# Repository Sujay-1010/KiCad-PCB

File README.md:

# KiCad-PCB
All the projects given have their pcb designing as well as their schematics attached.

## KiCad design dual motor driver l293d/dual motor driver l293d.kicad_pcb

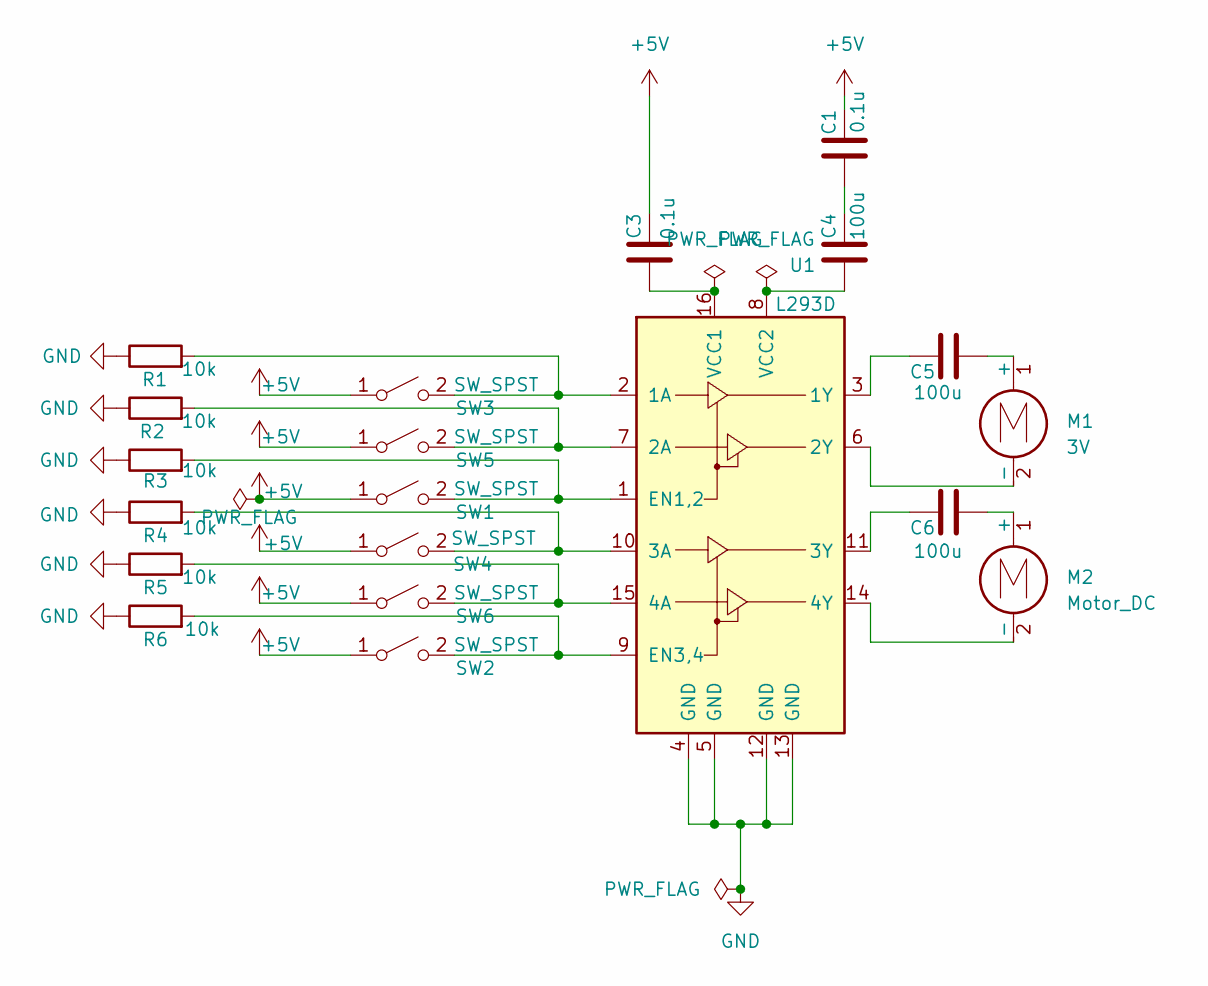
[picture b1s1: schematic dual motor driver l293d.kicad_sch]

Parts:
C1, C3: 0.1u; CP_Axial_L10.0mm_D6.0mm_P15.00mm_Horizontal
C4, C5, C6: 100u; CP_Axial_L10.0mm_D6.0mm_P15.00mm_Horizontal
M1: 3V; Vybronics_VZ30C1T8219732L
M2: Motor_DC; Vybronics_VZ30C1T8219732L
R1, R2, R3, R4, R5, R6: 10k; resistor
SW1, SW2, SW3, SW4, SW5, SW6: SW_SPST; SW_Push_1P1T_NO_CK_KMR2
U1: L293D; DIP-16_W7.62mm

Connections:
+5V: C1.2, C3.2, SW1.1 (A), SW2.1 (A), SW3.1 (A), SW4.1 (A), SW5.1 (A), SW6.1 (A)
GND: R1.1, R2.1, R3.1, R4.1, R5.1, R6.1, U1.4 (GND), U1.5 (GND), U1.12 (GND), U1.13 (GND)
unnamed: C1.1, C4.2
unnamed: C5.1, M1.1 (+)
unnamed: M1.2 (-), U1.6 (2Y)
unnamed: C6.1, M2.1 (+)
unnamed: M2.2 (-), U1.14 (4Y)
unnamed: R3.2, SW1.2 (B), U1.1 (EN1,2)
unnamed: R6.2, SW2.2 (B), U1.9 (EN3,4)
unnamed: R1.2, SW3.2 (B), U1.2 (1A)
unnamed: R4.2, SW4.2 (B), U1.10 (3A)
unnamed: R2.2, SW5.2 (B), U1.7 (2A)
unnamed: R5.2, SW6.2 (B), U1.15 (4A)
unnamed: C5.2, U1.3 (1Y)
unnamed: C6.2, U1.11 (3Y)
unnamed: C3.1, U1.16 (VCC1)
unnamed: C4.1, U1.8 (VCC2)

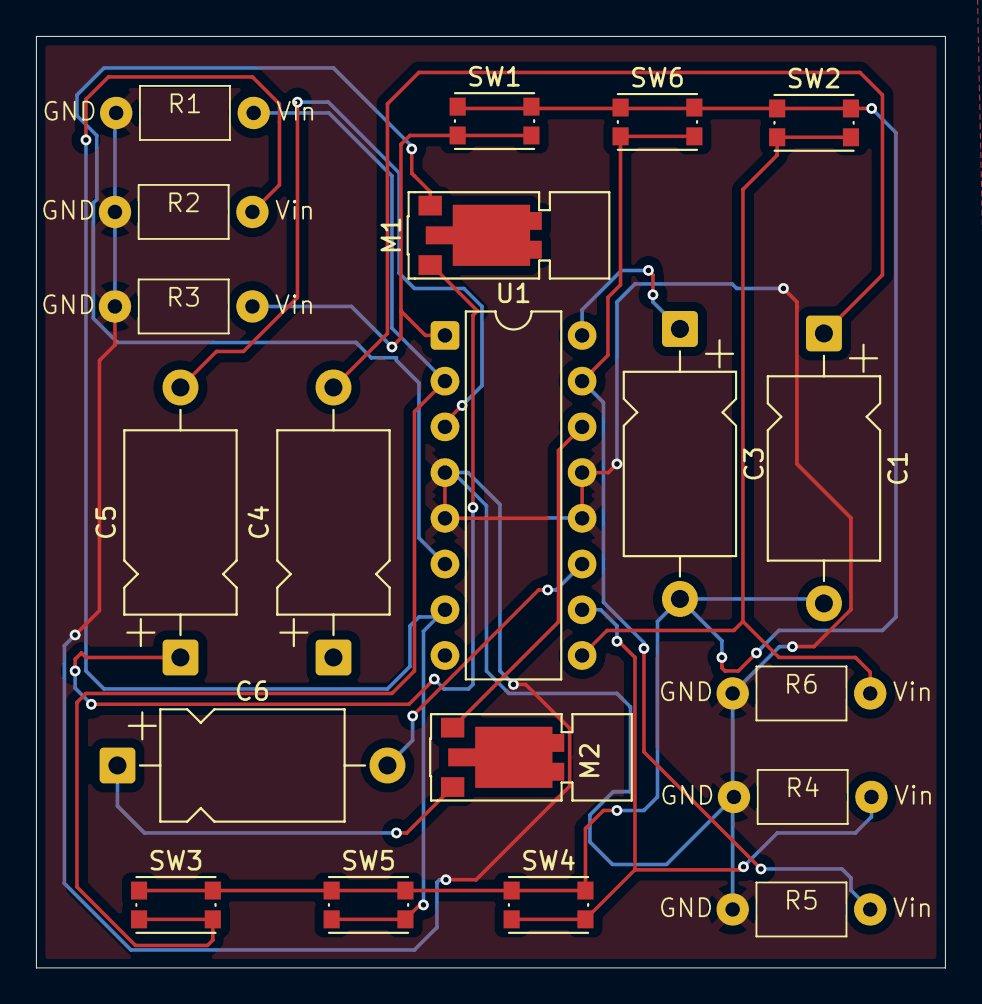
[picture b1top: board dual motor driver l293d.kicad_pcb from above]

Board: 2 copper layers, 50.5 x 51.8 mm, 20 parts (0 on the bottom side), 17 nets.

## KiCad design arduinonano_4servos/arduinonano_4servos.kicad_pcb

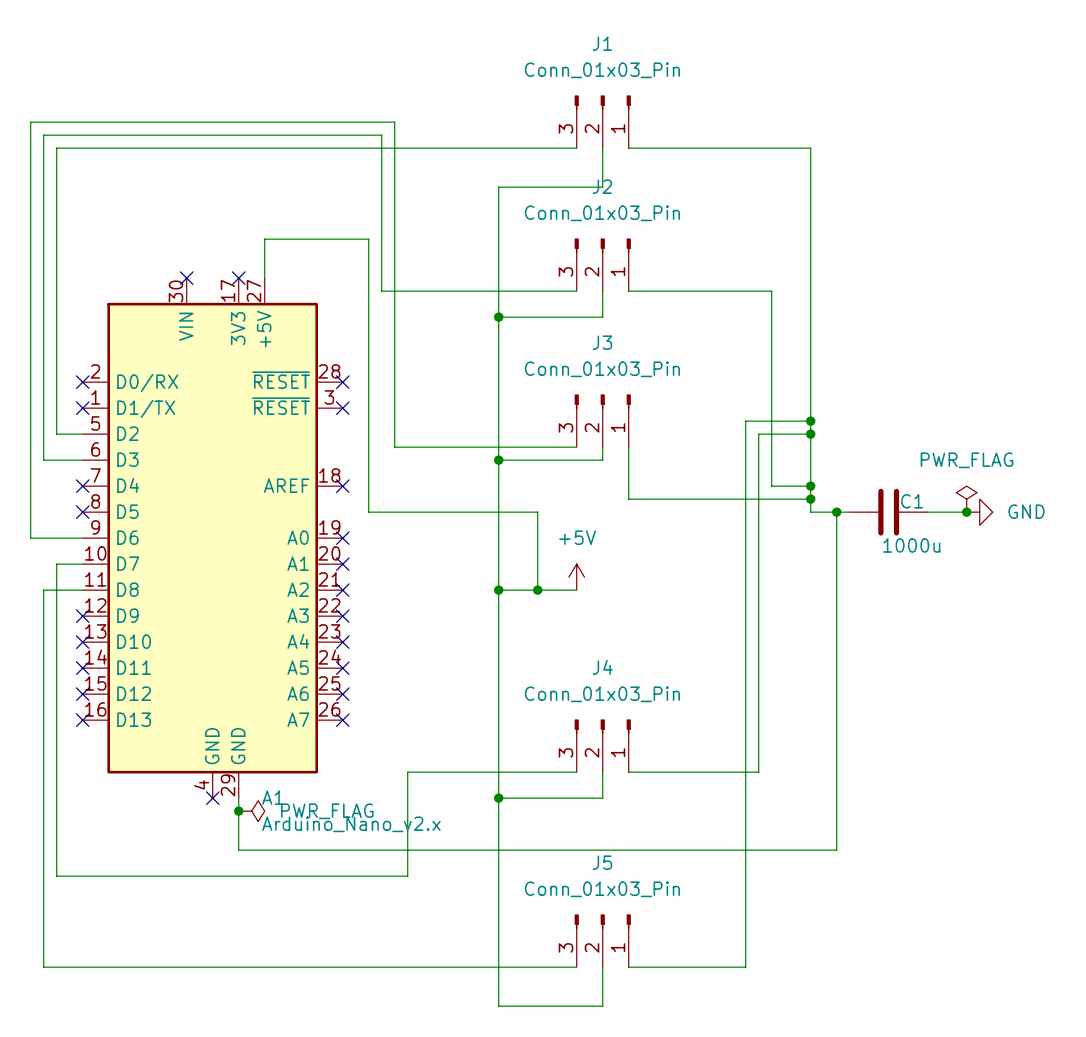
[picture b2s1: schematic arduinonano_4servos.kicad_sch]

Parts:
A1: Arduino_Nano_v2.x; Arduino_Nano
C1: 1000u; C_Disc_D6.0mm_W2.5mm_P5.00mm
J1, J2, J3, J4, J5: Conn_01x03_Pin; PinHeader_1x03_P2.54mm_Vertical

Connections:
+5V: A1.27 (+5V), J1.2, J2.2, J3.2, J4.2, J5.2
GND: C1.2
unnamed: A1.5 (D2), J1.3
unnamed: A1.6 (D3), J2.3
unnamed: A1.9 (D6), J3.3
unnamed: A1.10 (D7), J4.3
unnamed: A1.11 (D8), J5.3
unnamed: A1.29 (GND), C1.1, J1.1, J2.1, J3.1, J4.1, J5.1

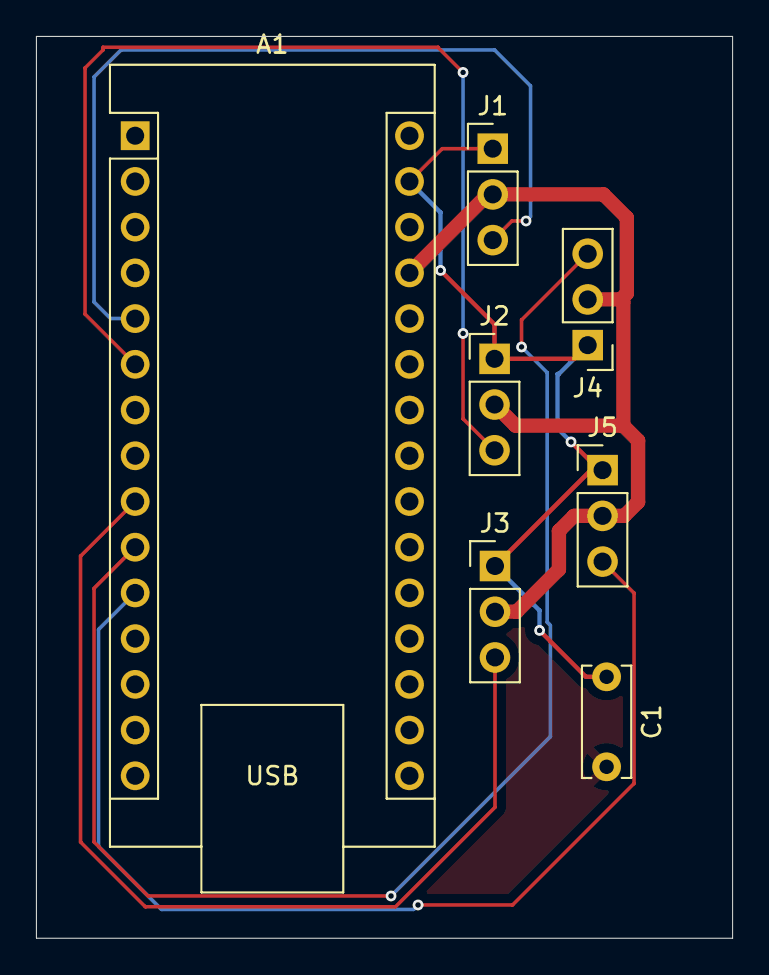
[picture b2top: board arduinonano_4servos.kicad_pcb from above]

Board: 2 copper layers, 38.7 x 50.1 mm, 7 parts (0 on the bottom side), 7 nets.

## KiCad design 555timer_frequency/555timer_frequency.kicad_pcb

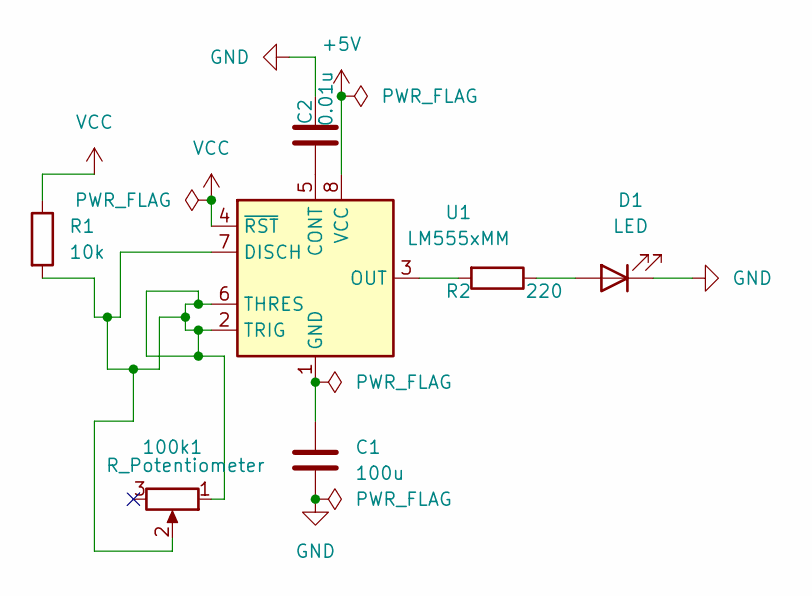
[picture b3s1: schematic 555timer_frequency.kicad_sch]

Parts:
100k1: R_Potentiometer; Potentiometer_ACP_CA9-H3,8_Horizontal
C1: 100u; C_Disc_D5.0mm_W2.5mm_P5.00mm
C2: 0.01u; C_Disc_D5.0mm_W2.5mm_P5.00mm
D1: LED; led
R1: 10k; resistor
R2: 220; resistor
U1: LM555xMM; VSSOP-8_3x3mm_P0.65mm

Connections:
+5V: U1.8 (VCC)
GND: C1.2, C2.2, D1.1 (K)
unnamed: D1.2 (A), R2.1
unnamed: C2.1, U1.5 (CONT)
unnamed: 100k1.1, 100k1.2, R1.2, U1.2 (TRIG), U1.6 (THRES), U1.7 (DISCH)
unnamed: C1.1, U1.1 (GND)
unnamed: R2.2, U1.3 (OUT)
VCC: R1.1, U1.4 (~RST)

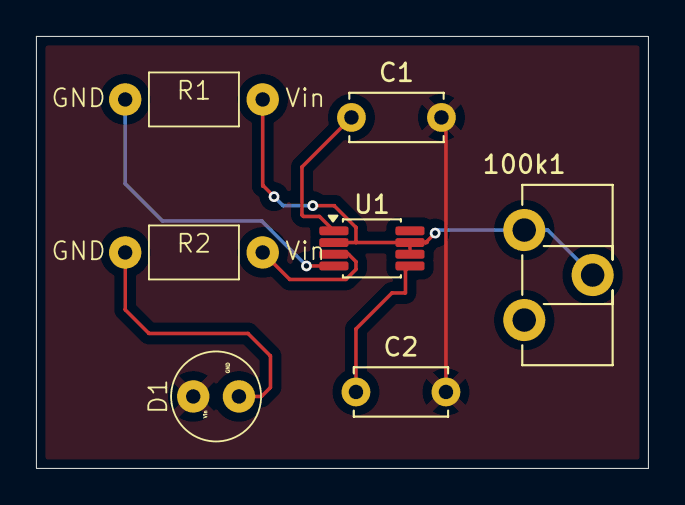
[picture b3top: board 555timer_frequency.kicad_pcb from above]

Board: 2 copper layers, 34.0 x 24.0 mm, 7 parts (0 on the bottom side), 7 nets.

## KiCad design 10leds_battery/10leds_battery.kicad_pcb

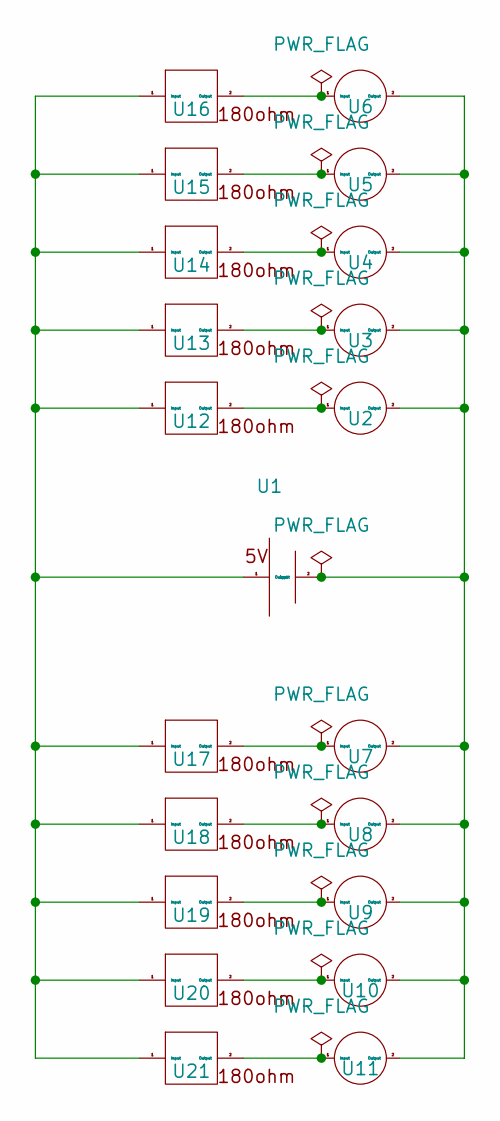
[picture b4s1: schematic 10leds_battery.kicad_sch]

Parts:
U1: battery
U2, U3, U4, U5, U6, U7, U8, U9, U10, U11: led
U12, U13, U14, U15, U16, U17, U18, U19, U20, U21: resistor

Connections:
unnamed: U1.2 (Input), U2.2 (Output), U3.2 (Output), U4.2 (Output), U5.2 (Output), U6.2 (Output), U7.2 (Output), U8.2 (Output), U9.2 (Output), U10.2 (Output), U11.2 (Output)
unnamed: U1.1 (Output), U12.1 (Input), U13.1 (Input), U14.1 (Input), U15.1 (Input), U16.1 (Input), U17.1 (Input), U18.1 (Input), U19.1 (Input), U20.1 (Input), U21.1 (Input)
unnamed: U10.1 (Input), U20.2 (Output)
unnamed: U11.1 (Input), U21.2 (Output)
unnamed: U2.1 (Input), U12.2 (Output)
unnamed: U3.1 (Input), U13.2 (Output)
unnamed: U4.1 (Input), U14.2 (Output)
unnamed: U5.1 (Input), U15.2 (Output)
unnamed: U6.1 (Input), U16.2 (Output)
unnamed: U7.1 (Input), U17.2 (Output)
unnamed: U8.1 (Input), U18.2 (Output)
unnamed: U9.1 (Input), U19.2 (Output)

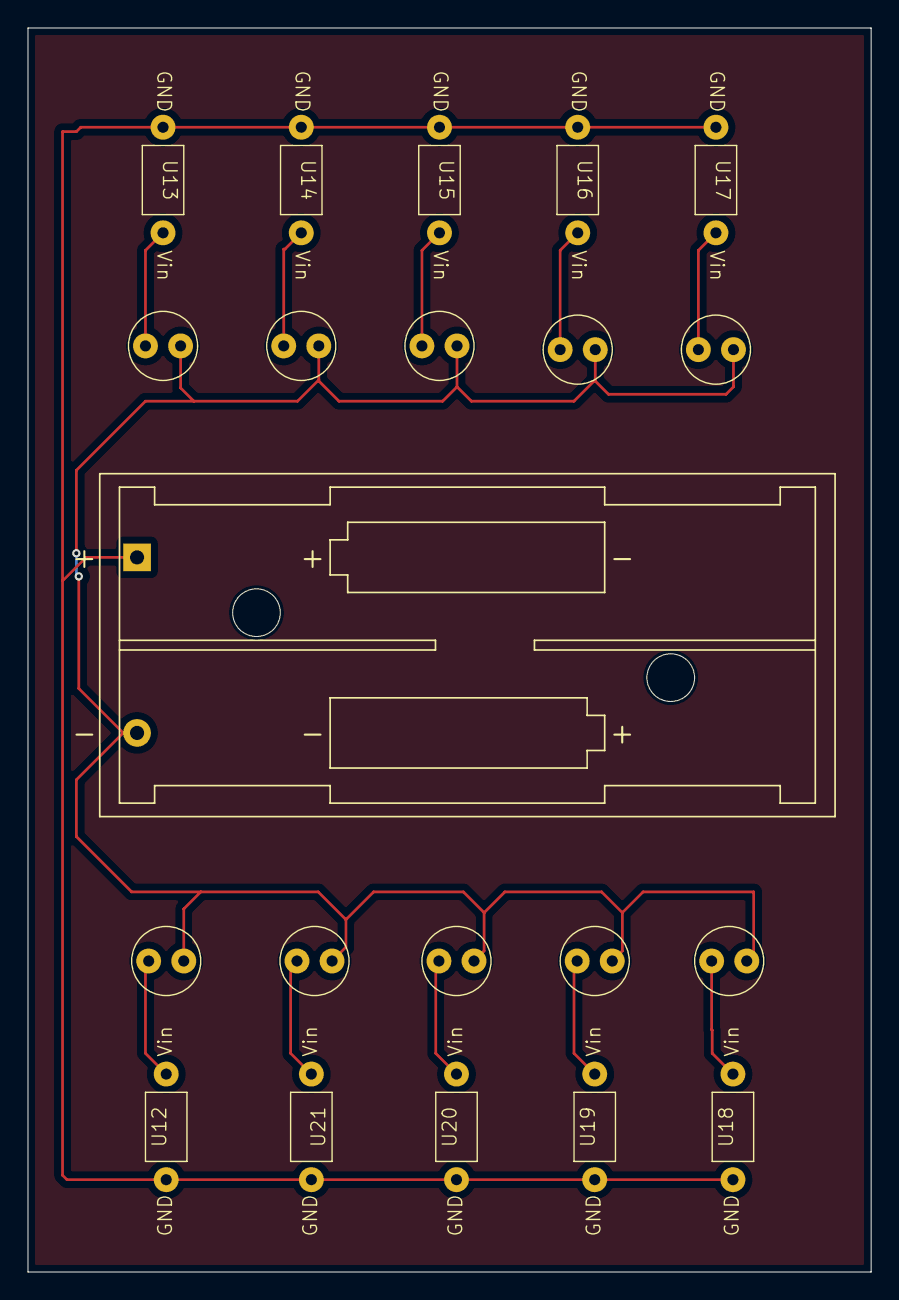
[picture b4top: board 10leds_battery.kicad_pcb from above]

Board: 2 copper layers, 61.0 x 90.0 mm, 21 parts (0 on the bottom side), 12 nets.

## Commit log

2026-05-27 Clarify description of PCB projects in README
